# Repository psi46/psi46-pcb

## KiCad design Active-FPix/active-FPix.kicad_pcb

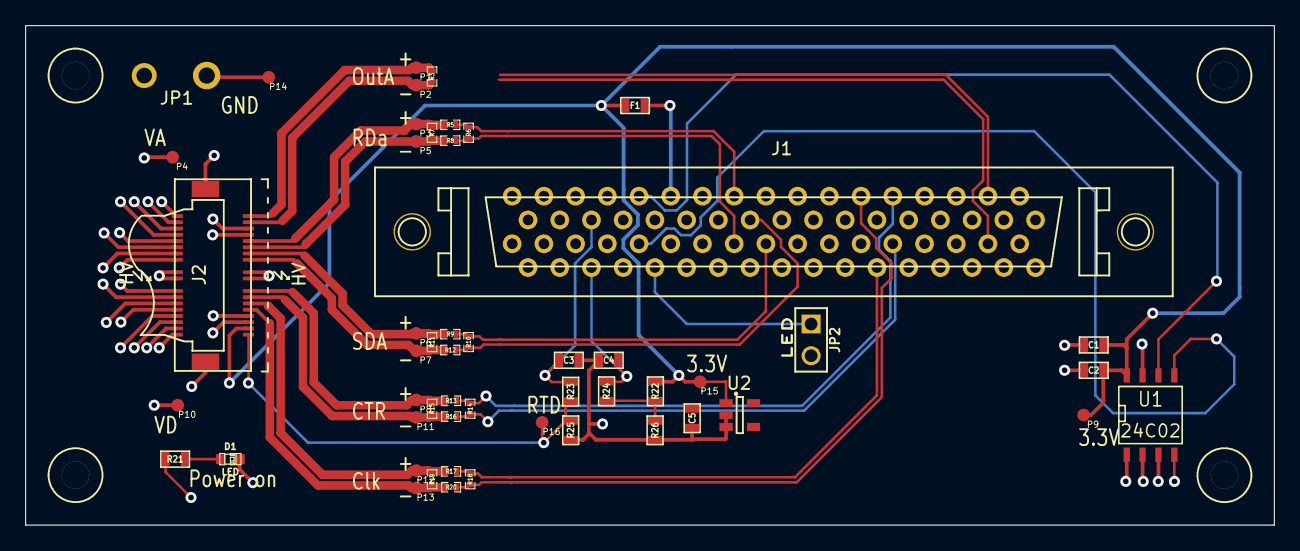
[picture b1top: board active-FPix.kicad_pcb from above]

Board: 4 copper layers, 100.0 x 40.0 mm, 56 parts (0 on the bottom side), 35 nets.

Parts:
C1, C3, C4: 100n; SM0603
C2: 1u; SM0603
C5: 1U; SM0603
D1: LED; LED-0603
F1: FUSE; SM0603
J1: CONN-SCSI68; SCSI68up
J2: CONN-SMK20; SMK20hv
JP1: JUMPER; HarwinShortLnk
JP2: JUMPER; PIN_ARRAY_2X1
P1: OutA+; testpad
P2: OutA-; testpad
P3: RDa+; testpad
P4: VA; testpad
P5: RDa-; testpad
P6: SDA+; testpad
P7: SDA-; testpad
P8: CTR+; testpad
P9: 3V3; testpad
P10: VD; testpad
P11: CTR-; testpad
P12: CLK+; testpad
P13: CLK-; testpad
P14: GND; testpad
P15: RTD+; testpad
P16: RTD-; testpad
R3: R; SM0402
R5, R8: 0; SM0402
R6, R10, R14, R18: 10G; SM0402
R7: 120; SM0402
R9, R12, R13, R16, R17, R20: 39; SM0402
R11, R15, R19: 91; SM0402
R21: 56; SM0603
R22, R25, R26: 10k 0.1%; SM0603
R23, R24: 10k 5%; SM0603
U1: 24C02; SO8N
U2: TPS769XX; SOT-23-5
loch: M2; lochM2
loch#2, loch#3, loch#4: M2; lochM2

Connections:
AIN0: C3.1, J1.57, R23.2
AIN1: C4.1, C5.1, J1.58, R24.2
CLK_n: J1.23, R18.2, R20.1
CLK_p: J1.22, R17.1, R18.1
CTR_n: J1.20, R14.2, R16.1
CTR_p: J1.19, R13.1, R14.1
GND: C1.2, C2.2, C3.2, C4.2, C5.2, J1.4, J1.6, J1.9, J1.15, J1.18, J1.21, J1.24, J1.30, J1.35, J1.38, J1.41, J1.46, J1.60, J1.64, J2.2, J2.4, J2.6, J2.8, J2.14, J2.16, J2.26, J2.28, J2.34, J2.36, J2.38, J2.40, J2.41, J2.42, JP1.1, JP1.2, P14.1, R25.2, R26.2, U1.1, U1.2, U1.3, U1.4, U1.7, U2.2, U2.3
HV: J1.68, J2.19, J2.20, J2.21, J2.22
I2C_SCL2: J1.51, U1.6
I2C_SDA2: J1.52, U1.5
unnamed: D1.1, R21.2
unnamed: F1.2, J1.47
unnamed: JP2.2, R21.1
unnamed: R22.1, R24.1, R26.1
POWER_ON: J1.50, JP2.1
RTD+: C1.1, C2.1, F1.1, J2.3, P9.1, P15.1, R22.2, U1.8, U2.1
RTD-: J2.1, P16.1, R23.1, R25.1
SDATA1_n: J1.8, R3.2
SDATA1_p: J1.7, R3.1
SDA_n: J1.37, R10.2, R12.1
SDA_p: J1.36, R9.1, R10.1
TBM_Clk_In+: J2.11, P12.1, R17.2, R19.2
TBM_Clk_In-: J2.9, P13.1, R19.1, R20.2
TBM_Out_A+: J2.39, P1.1
TBM_Out_A-: J2.37, P2.1
TBM_RDa_Out+: J2.31, P3.1, R5.2, R7.1
TBM_RDa_Out-: J2.29, P5.1, R7.2, R8.2
TBM_SD_In+: J2.27, P6.1, R9.2, R11.1
TBM_SD_In-: J2.25, P7.1, R11.2, R12.2
TBM_Trig_In+: J2.15, P8.1, R13.2, R15.1
TBM_Trig_In-: J2.13, P11.1, R15.2, R16.2
TOUT_n: J1.40, R6.2, R8.1
TOUT_p: J1.39, R5.1, R6.1
VA: J1.25, J1.26, J1.27, J1.28, J2.30, J2.32, J2.33, J2.35, P4.1
VD: J1.29, J1.42, J1.43, J1.44, J1.45, J2.5, J2.7, J2.10, J2.12, P10.1

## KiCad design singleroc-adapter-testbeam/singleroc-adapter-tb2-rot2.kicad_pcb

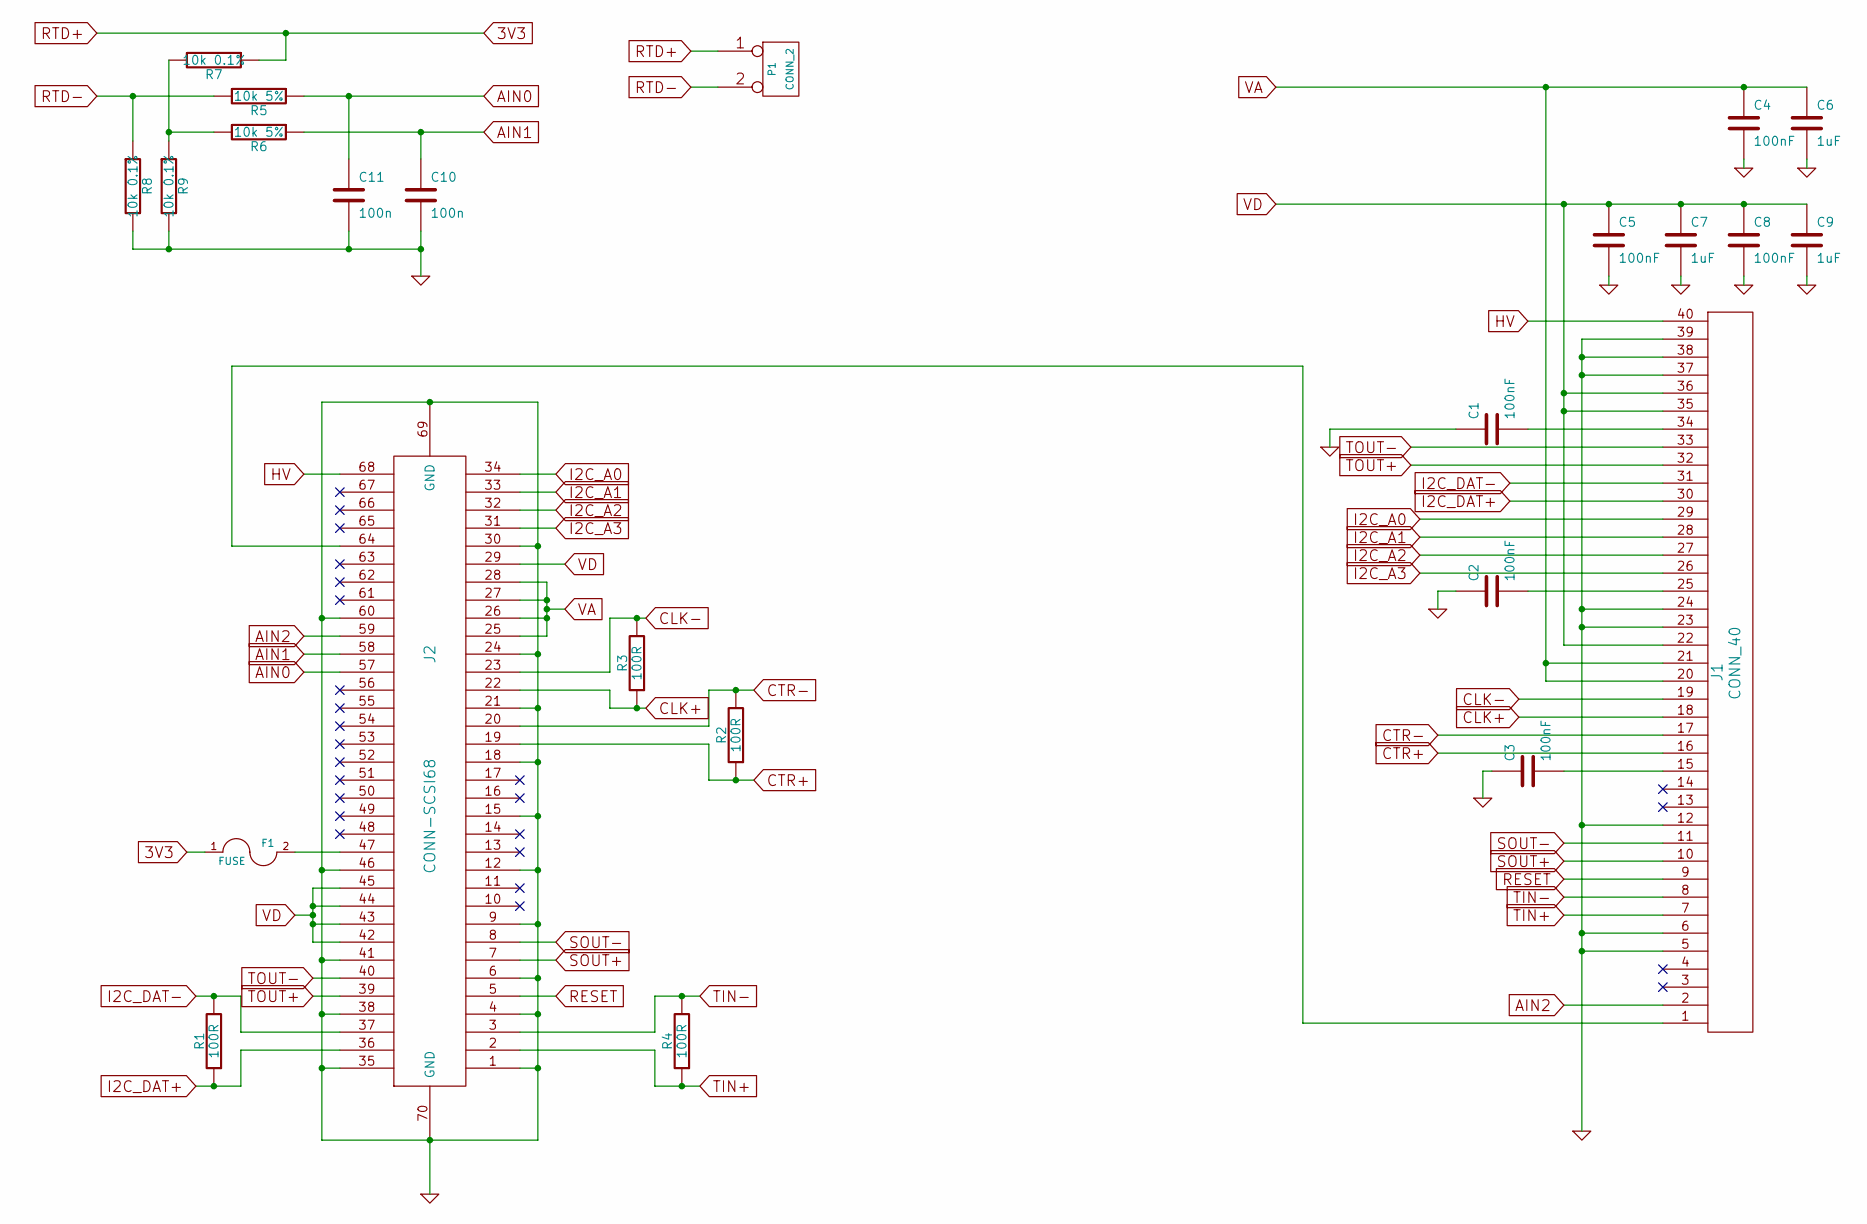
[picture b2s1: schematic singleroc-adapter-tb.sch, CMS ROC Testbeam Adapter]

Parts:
C1, C2, C3, C4, C5, C8: 100nF
C6, C7, C9: 1uF
C10, C11: 100n
F1: FUSE
J1: CONN_40
J2: CONN-SCSI68
P1: CONN_2
R1, R2, R3, R4: 100R
R5, R6: 10k 5%
R7, R8, R9: 10k 0.1%

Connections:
AIN0: C11.1, J2.57, R5.1
AIN1: C10.1, J2.58, R6.1
AIN2: J1.2, J2.59
CLK+: J1.18, J2.22, R3.1
CLK-: J1.19, J2.23, R3.2
CTR+: J1.16, J2.19, R2.1
CTR-: J1.17, J2.20, R2.2
GND: C1.1, C2.1, C3.1, C4.2, C5.2, C6.2, C7.2, C8.2, C9.2, C10.2, C11.2, J1.5, J1.6, J1.12, J1.23, J1.24, J1.37, J1.38, J1.39, J2.1, J2.4, J2.6, J2.9, J2.12, J2.15, J2.18, J2.21, J2.24, J2.30, J2.35, J2.38, J2.41, J2.46, J2.60, J2.69 (GND), J2.70 (GND), R8.2, R9.2
HV: J1.40, J2.68
I2C_A0: J1.29, J2.34
I2C_A1: J1.28, J2.33
I2C_A2: J1.27, J2.32
I2C_A3: J1.26, J2.31
I2C_DAT+: J1.30, J2.36, R1.1
I2C_DAT-: J1.31, J2.37, R1.2
unnamed: C1.2, J1.34
unnamed: C2.2, J1.25
unnamed: C3.2, J1.15
unnamed: F1.2, J2.47
unnamed: J1.1, J2.64
unnamed: R6.2, R7.2, R9.1
RESET: J1.9, J2.5
RTD+: F1.1, P1.1, R7.1
RTD-: P1.2 (PM), R5.2, R8.1
SOUT+: J1.10, J2.7
SOUT-: J1.11, J2.8
TIN+: J1.7, J2.2, R4.1
TIN-: J1.8, J2.3, R4.2
TOUT+: J1.32, J2.39
TOUT-: J1.33, J2.40
VA: C4.1, C6.1, J1.20, J1.21, J2.25, J2.26, J2.27, J2.28
VD: C5.1, C7.1, C8.1, C9.1, J1.22, J1.35, J1.36, J2.29, J2.42, J2.43, J2.44, J2.45

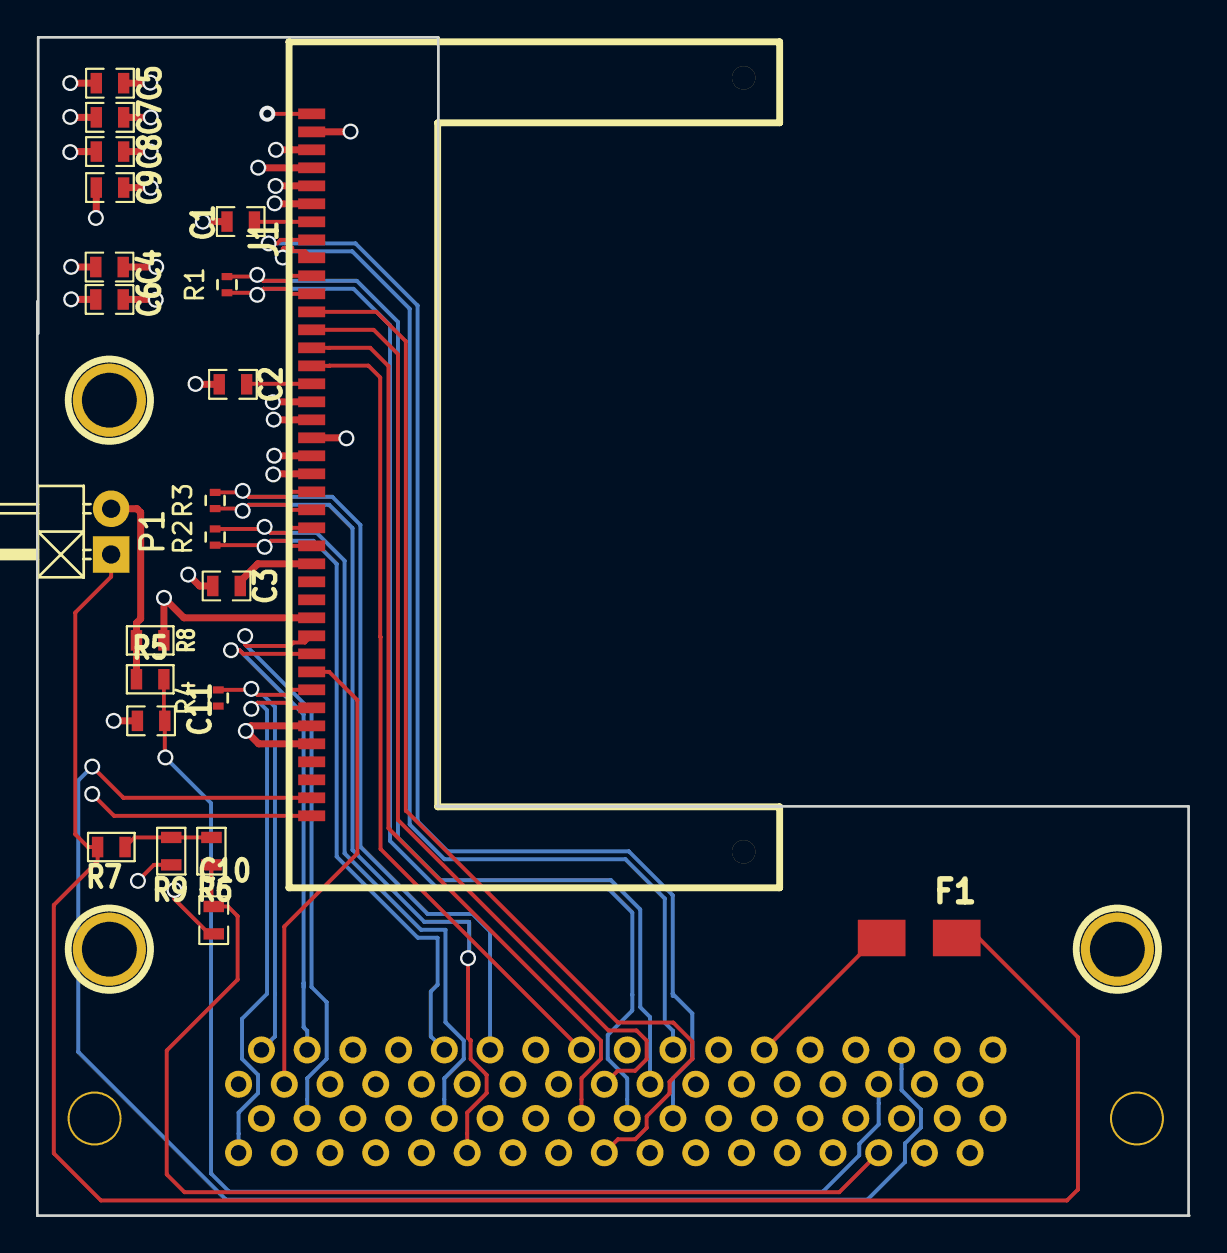
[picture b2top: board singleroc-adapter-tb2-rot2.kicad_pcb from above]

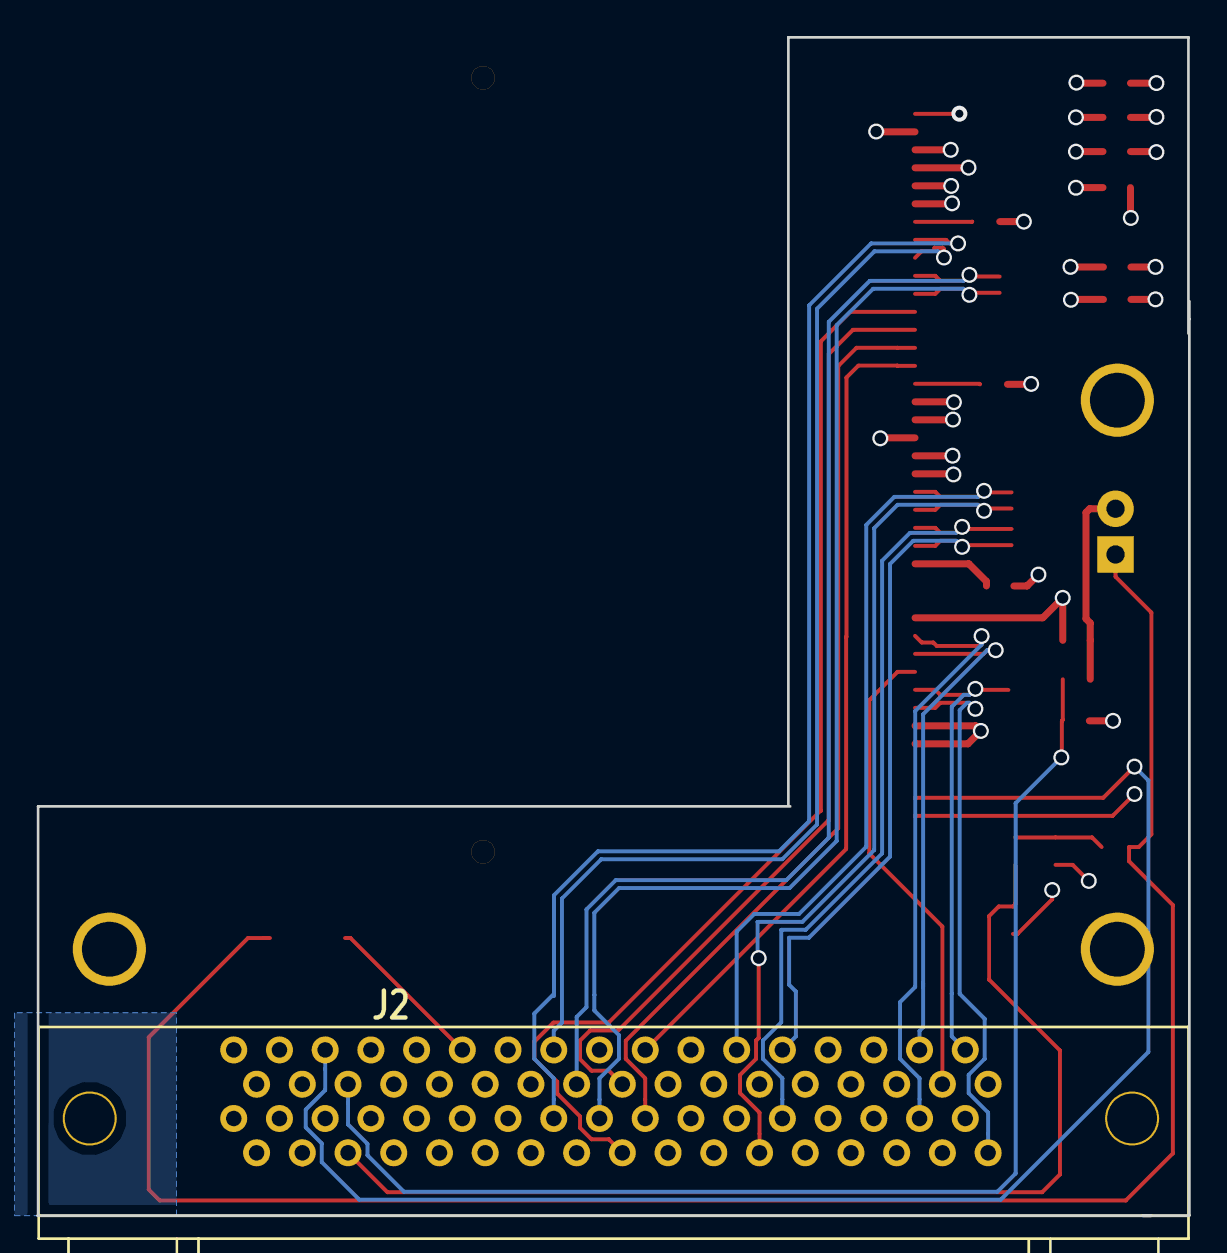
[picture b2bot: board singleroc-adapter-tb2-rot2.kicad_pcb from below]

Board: 4 copper layers, 64.0 x 65.5 mm, 24 parts (2 on the bottom side), 32 nets.

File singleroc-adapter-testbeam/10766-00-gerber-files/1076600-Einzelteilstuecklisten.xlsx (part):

DESY- ZE - AV |  |  |  |  | Baugruppenbenennung : | CMS ROC Testbeam Adapter |  |  |  |  | In Spalte (B) Bauteil Position = ist freigegeben
(C) DESY 2010, DESY behält sich alle Rechte vor. Schutzvermerk ISO 16016 beacht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 |  |  |  |  | Baugruppenenummer : |  |  |  |  |  | Gesamte Zeile = Bauteil wird nicht bestückt
 |  |  |  |  | gehört zu : |  |  |  |  |  | Kritisch |  | Geändert |  |  | Unklar
 |  |  |  |  | Ersteller : | S. Spannagel |  |  |  |  |  |  |  |  |  | RoHS Nein (X)
 |  |  |  |  | Erstellungsdatum : | 13/10/2014 |  |  |  |  |  |  |  |  |  | Bei VE = m,mm,kg oder g Menge angeben
Pos | Bauteil Position | Bauteil Art / Ort | Bau- form | Orderbase Artikelnr | Benennung / Type / Wert | Hersteller | Hersteller-Nr. | Lieferant | Lieferanten-Nr. | Preis / VE in € | Preis / n Stück | VE | Menge / VE | (X) |  | Bemerkungen
1 | J1 | T | SMD |  | Edge Connector w/ Card Guides, 40-Pin, Type 02 for 1,6mm PCBs | Samtec | MB1-140-01-L-S-02-SL | Farnell | 2097301 | 11.97 | 1 | St | 1 |  | 0
2 | J2 | B | THT |  | SCSI 68pin Connector, 90deg | Multicomp | 8AL068S-325F1-AN | Farnell | 1099270 |  | 1 | St | 1 |  | 0
3 | F1 | B | SMD |  | Fuse |  |  |  |  |  | 1 | St | 1 |  | 0 | Bauteil wird nicht bestueckt.
4 | R1 | B | SMD |  | Widerstand SMD0603 100R, Toleranz 1% | Yaego/ Vishay | RC0603FR07 100r L | ZE |  |  | 1 | St | 1 |  | 0
5 | R2 | B | SMD |  | Widerstand SMD0603 100R, Toleranz 1% | Yaego/ Vishay | RC0603FR07 100r L | ZE |  |  | 1 | St | 1 |  | 0
6 | R3 | B | SMD |  | Widerstand SMD0603 100R, Toleranz 1% | Yaego/ Vishay | RC0603FR07 100r L | ZE |  |  | 1 | St | 1 |  | 0
7 | R4 | B | SMD |  | Widerstand SMD0603 100R, Toleranz 1% | Yaego/ Vishay | RC0603FR07 100r L | ZE |  |  | 1 | St | 1 |  | 0
8 | R5 | B | SMD |  | Widerstand SMD0603 10k, Toleranz 1% | Yaego/ Vishay | RC0603FR07 10k L | ZE |  |  | 1 | St | 1 |  | 0
9 | R6 | B | SMD |  | Widerstand SMD0603 10k, Toleranz 1% | Yaego/ Vishay | RC0603FR07 10k L | ZE |  |  | 1 | St | 1 |  | 0
10 | R7 | B | SMD |  | Widerstand SMD0603 10k, Toleranz 0,1% |  |  |  |  |  | 1 | St | 1 |  | 0
11 | R8 | B | SMD |  | Widerstand SMD0603 10k, Toleranz 0,1% |  |  |  |  |  | 1 | St | 1 |  | 0
12 | R9 | B | SMD |  | Widerstand SMD0603 10k, Toleranz 0,1% |  |  |  |  |  | 1 | St | 1 |  | 0
13 | C1 | B | SMD |  | Kapazitaet SMD0603 100nF, Toleranz 10% | TDK | C1608 X7R 1H104KT | ZE |  |  | 1 | St | 1 |  | 0
14 | C2 | B | SMD |  | Kapazitaet SMD0603 100nF, Toleranz 10% | TDK | C1608 X7R 1H104KT | ZE |  |  | 1 | St | 1 |  | 0
15 | C3 | B | SMD |  | Kapazitaet SMD0603 100nF, Toleranz 10% | TDK | C1608 X7R 1H104KT | ZE |  |  | 1 | St | 1 |  | 0
16 | C4 | B | SMD |  | Kapazitaet SMD0603 100nF, Toleranz 10% | TDK | C1608 X7R 1H104KT | ZE |  |  | 1 | St | 1 |  | 0
17 | C5 | B | SMD |  | Kapazitaet SMD0603 100nF, Toleranz 10% | TDK | C1608 X7R 1H104KT | ZE |  |  | 1 | St | 1 |  | 0
18 | C6 | B | SMD |  | Kapazitaet SMD0603 1uF, Toleranz 10% |  |  |  |  |  | 1 | St | 1 |  | 0
19 | C7 | B | SMD |  | Kapazitaet SMD0603 1uF, Toleranz 10% |  |  |  |  |  | 1 | St | 1 |  | 0
20 | C8 | B | SMD |  | Kapazitaet SMD0603 100nF, Toleranz 10% | TDK | C1608 X7R 1H104KT | ZE |  |  | 1 | St | 1 |  | 0
21 | C9 | B | SMD |  | Kapazitaet SMD0603 1uF, Toleranz 10% |  |  |  |  |  | 1 | St | 1 |  | 0
22 | C10 | B | SMD |  | Kapazitaet SMD0603 100nF, Toleranz 10% | TDK | C1608 X7R 1H104KT | ZE |  |  | 1 | St | 1 |  | 0
23 | C11 | B | SMD |  | Kapazitaet SMD0603 100nF, Toleranz 10% | TDK | C1608 X7R 1H104KT | ZE |  |  | 1 | St | 1 |  | 0
24 | P1 | B | THT |  | Stiftleiste, 1x2 Pins, 90deg, Pitch 2,54mm | Molex | 22-12-4022 | Farnell | 1360142 |  | 1 | St | 1 |  | 0
25 |  | LP |  |  | Leiterplatte 10766-00 |  |  |  |  |  | 1 | St | 1 |  | 0
26 |  |  |  |  |  |  |  |  |  |  | 1 | St | 1 |  | 0
27 |  |  |  |  |  |  |  |  |  |  | 1 | St | 1 |  | 0
28 |  |  |  |  |  |  |  |  |  |  | 1 | St | 1 |  | 0
29 |  |  |  |  |  |  |  |  |  |  | 1 | St | 1 |  | 0
30 |  |  |  |  |  |  |  |  |  |  | 1 | St | 1 |  | 0
31 |  |  |  |  |  |  |  |  |  |  | 1 | St | 1 |  | 0
32 |  |  |  |  |  |  |  |  |  |  | 1 | St | 1 |  | 0
33 |  |  |  |  |  |  |  |  |  |  | 1 | St | 1 |  | 0
34 |  |  |  |  |  |  |  |  |  |  | 1 | St | 1 |  | 0
35 |  |  |  |  |  |  |  |  |  |  | 1 | St | 1 |  | 0
36 |  |  |  |  |  |  |  |  |  |  | 1 | St | 1 |  | 0
37 |  |  |  |  |  |  |  |  |  |  | 1 | St | 1 |  | 0
38 |  |  |  |  |  |  |  |  |  |  | 1 | St | 1 |  | 0
39 |  |  |  |  |  |  |  |  |  |  | 1 | St | 1 |  | 0
40 |  |  |  |  |  |  |  |  |  |  | 1 | St | 1 |  | 0
41 |  |  |  |  |  |  |  |  |  |  | 1 | St | 1 |  | 0
42 |  |  |  |  |  |  |  |  |  |  | 1 | St | 1 |  | 0
43 |  |  |  |  |  |  |  |  |  |  | 1 | St | 1 |  | 0
44 |  |  |  |  |  |  |  |  |  |  | 1 | St | 1 |  | 0
45 |  |  |  |  |  |  |  |  |  |  | 1 | St | 1 |  | 0
46 |  |  |  |  |  |  |  |  |  |  | 1 | St | 1 |  | 0
47 |  |  |  |  |  |  |  |  |  |  | 1 | St | 1 |  | 0
48 |  |  |  |  |  |  |  |  |  |  | 1 | St | 1 |  | 0
49 |  |  |  |  |  |  |  |  |  |  | 1 | St | 1 |  | 0
50 |  |  |  |  |  |  |  |  |  |  | 1 | St | 1 |  | 0
51 |  |  |  |  |  |  |  |  |  |  | 1 | St | 1 |  | 0
52 |  |  |  |  |  |  |  |  |  |  | 1 | St | 1 |  | 0
53 |  |  |  |  |  |  |  |  |  |  | 1 | St | 1 |  | 0
54 |  |  |  |  |  |  |  |  |  |  | 1 | St | 1 |  | 0
55 |  |  |  |  |  |  |  |  |  |  | 1 | St | 1 |  | 0
56 |  |  |  |  |  |  |  |  |  |  | 1 | St | 1 |  | 0
57 |  |  |  |  |  |  |  |  |  |  | 1 | St | 1 |  | 0
58 |  |  |  |  |  |  |  |  |  |  | 1 | St | 1 |  | 0
59 |  |  |  |  |  |  |  |  |  |  | 1 | St | 1 |  | 0
60 |  |  |  |  |  |  |  |  |  |  | 1 | St | 1 |  | 0
61 |  |  |  |  |  |  |  |  |  |  | 1 | St | 1 |  | 0
62 |  |  |  |  |  |  |  |  |  |  | 1 | St | 1 |  | 0
63 |  |  |  |  |  |  |  |  |  |  | 1 | St | 1 |  | 0
64 |  |  |  |  |  |  |  |  |  |  | 1 | St | 1 |  | 0
65 |  |  |  |  |  |  |  |  |  |  | 1 | St | 1 |  | 0
66 |  |  |  |  |  |  |  |  |  |  | 1 | St | 1 |  | 0
67 |  |  |  |  |  |  |  |  |  |  | 1 | St | 1 |  | 0
68 |  |  |  |  |  |  |  |  |  |  | 1 | St | 1 |  | 0
69 |  |  |  |  |  |  |  |  |  |  | 1 | St | 1 |  | 0
70 |  |  |  |  |  |  |  |  |  |  | 1 | St | 1 |  | 0
71 |  |  |  |  |  |  |  |  |  |  | 1 | St | 1 |  | 0
72 |  |  |  |  |  |  |  |  |  |  | 1 | St | 1 |  | 0
73 |  |  |  |  |  |  |  |  |  |  | 1 | St | 1 |  | 0
74 |  |  |  |  |  |  |  |  |  |  | 1 | St | 1 |  | 0
75 |  |  |  |  |  |  |  |  |  |  | 1 | St | 1 |  | 0
76 |  |  |  |  |  |  |  |  |  |  | 1 | St | 1 |  | 0
77 |  |  |  |  |  |  |  |  |  |  | 1 | St | 1 |  | 0
78 |  |  |  |  |  |  |  |  |  |  | 1 | St | 1 |  | 0
79 |  |  |  |  |  |  |  |  |  |  | 1 | St | 1 |  | 0
80 |  |  |  |  |  |  |  |  |  |  | 1 | St | 1 |  | 0
81 |  |  |  |  |  |  |  |  |  |  | 1 | St | 1 |  | 0
82 |  |  |  |  |  |  |  |  |  |  | 1 | St | 1 |  | 0
83 |  |  |  |  |  |  |  |  |  |  | 1 | St | 1 |  | 0
84 |  |  |  |  |  |  |  |  |  |  | 1 | St | 1 |  | 0
85 |  |  |  |  |  |  |  |  |  |  | 1 | St | 1 |  | 0
86 |  |  |  |  |  |  |  |  |  |  | 1 | St | 1 |  | 0
87 |  |  |  |  |  |  |  |  |  |  | 1 | St | 1 |  | 0
88 |  |  |  |  |  |  |  |  |  |  | 1 | St | 1 |  | 0
89 |  |  |  |  |  |  |  |  |  |  | 1 | St | 1 |  | 0
90 |  |  |  |  |  |  |  |  |  |  | 1 | St | 1 |  | 0
91 |  |  |  |  |  |  |  |  |  |  | 1 | St | 1 |  | 0
92 |  |  |  |  |  |  |  |  |  |  | 1 | St | 1 |  | 0
93 |  |  |  |  |  |  |  |  |  |  | 1 | St | 1 |  | 0
94 |  |  |  |  |  |  |  |  |  |  | 1 | St | 1 |  | 0
95 |  |  |  |  |  |  |  |  |  |  | 1 | St | 1 |  | 0
96 |  |  |  |  |  |  |  |  |  |  | 1 | St | 1 |  | 0
97 |  |  |  |  |  |  |  |  |  |  | 1 | St | 1 |  | 0
98 |  |  |  |  |  |  |  |  |  |  | 1 | St | 1 |  | 0
99 |  |  |  |  |  |  |  |  |  |  | 1 | St | 1 |  | 0
100 |  |  |  |  |  |  |  |  |  |  | 1 | St | 1 |  | 0
101 |  |  |  |  |  |  |  |  |  |  | 1 | St | 1 |  | 0
102 |  |  |  |  |  |  |  |  |  |  | 1 | St | 1 |  | 0
103 |  |  |  |  |  |  |  |  |  |  | 1 | St | 1 |  | 0
104 |  |  |  |  |  |  |  |  |  |  | 1 | St | 1 |  | 0
105 |  |  |  |  |  |  |  |  |  |  | 1 | St | 1 |  | 0
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
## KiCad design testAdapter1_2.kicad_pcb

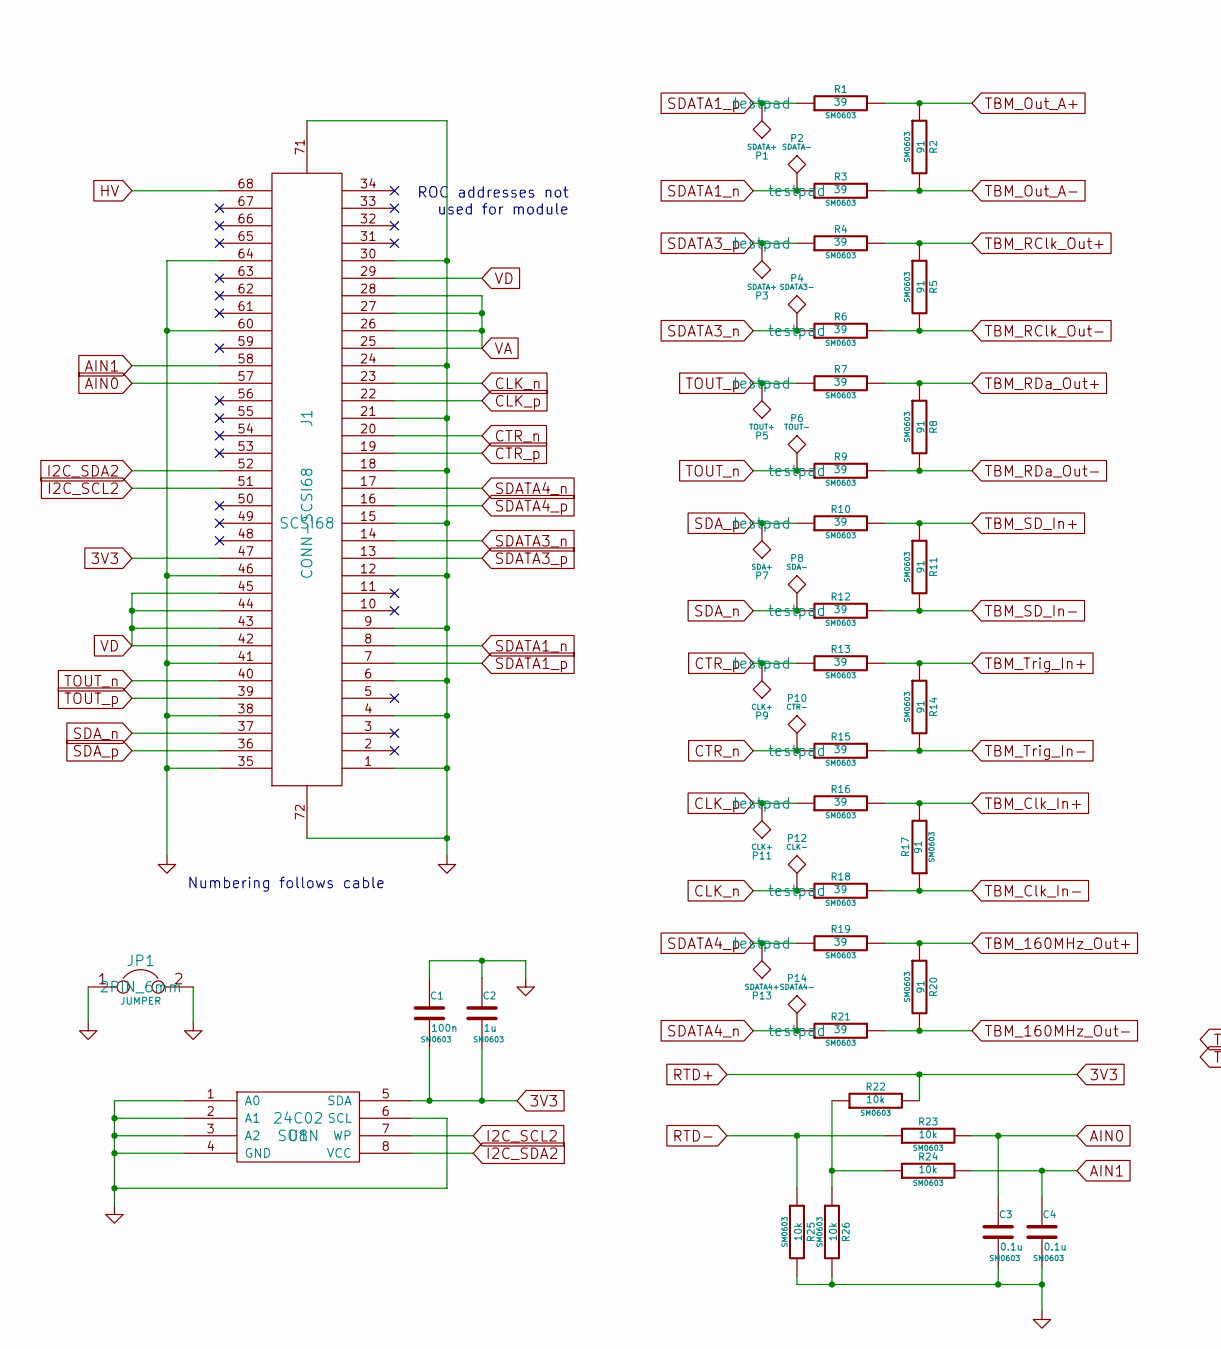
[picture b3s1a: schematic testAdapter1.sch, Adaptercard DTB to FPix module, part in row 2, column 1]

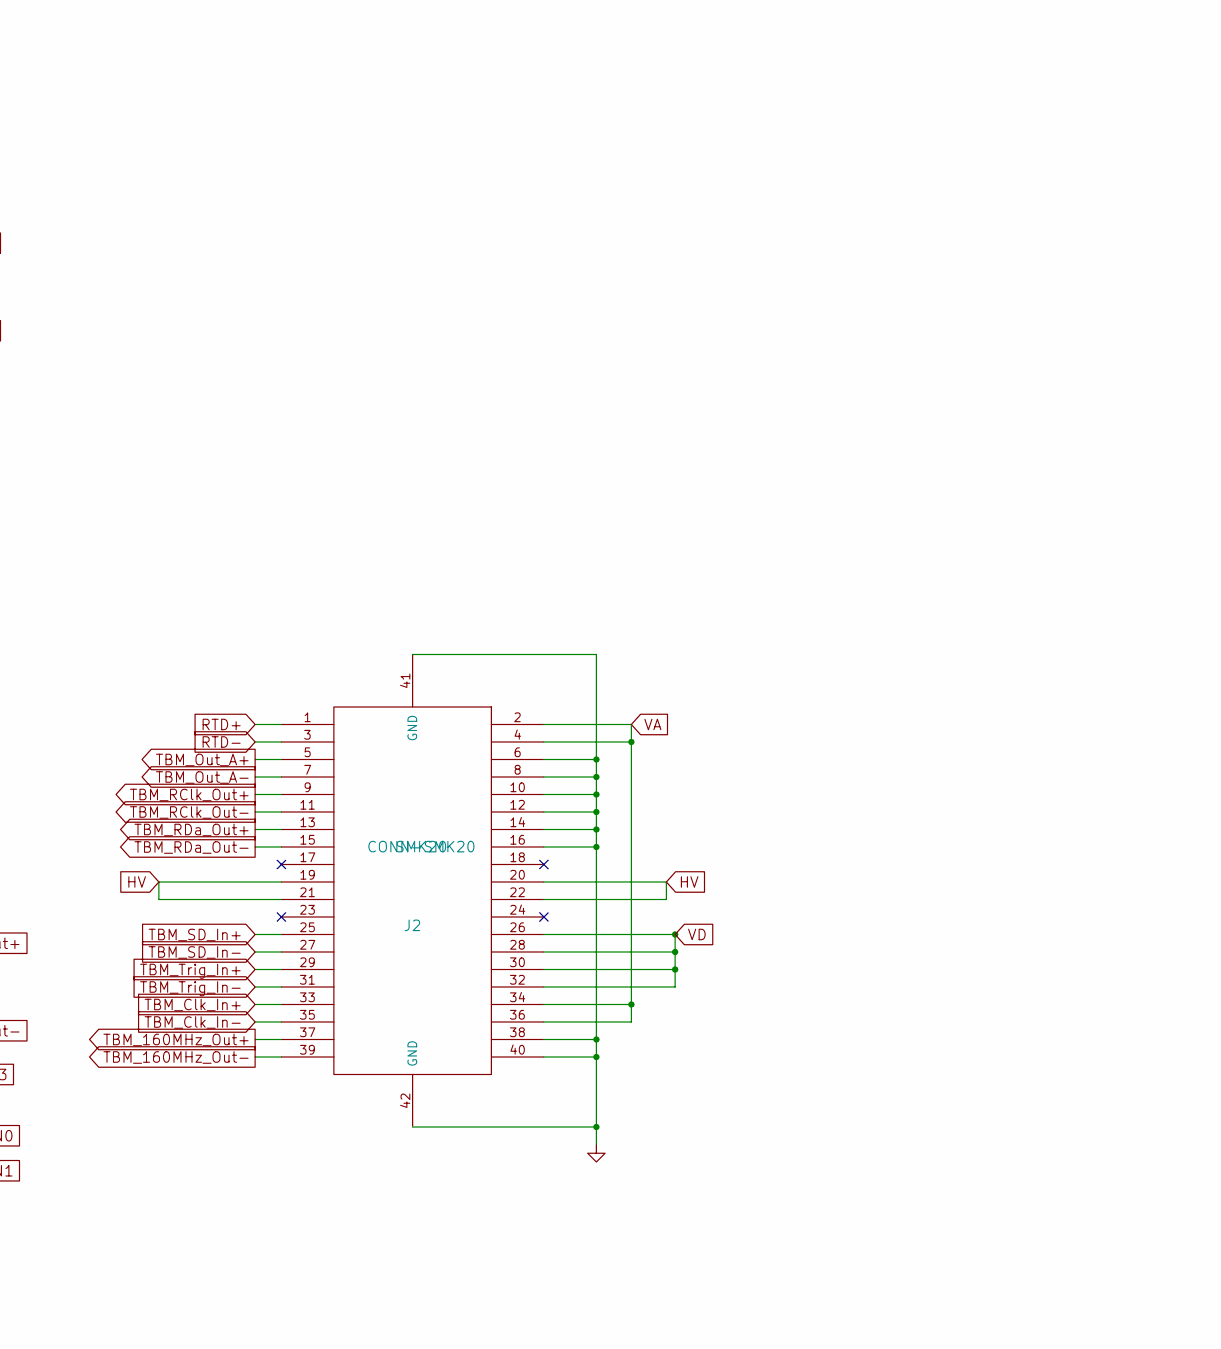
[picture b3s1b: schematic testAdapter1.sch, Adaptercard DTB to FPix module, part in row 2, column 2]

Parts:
C1: 100n; SM0603
C2: 1u; SM0603
C3, C4: 0.1u; SM0603
J1: CONN-SCSI68; SCSI68
J2: CONN-SMK20; SMK20
JP1: JUMPER; 2PIN_6mm
P1, P3: SDATA+; testpad
P2: SDATA-; testpad
P4: SDATA3-; testpad
P5: TOUT+; testpad
P6: TOUT-; testpad
P7: SDA+; testpad
P8: SDA-; testpad
P9, P11: CLK+; testpad
P10: CTR-; testpad
P12: CLK-; testpad
P13: SDATA4+; testpad
P14: SDATA4-; testpad
R1, R3, R4, R6, R7, R9, R10, R12, R13, R15, R16, R18, R19, R21: 39; SM0603
R2, R5, R8, R11, R14, R17, R20: 91; SM0603
R22, R23, R24, R25, R26: 10k; SM0603
U1: 24C02; SO8N

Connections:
3V3: C1.2, C2.2, J1.47, J2.1, R22.2, U1.5 (SDA)
AIN0: C3.1, J1.57, R23.2
AIN1: C4.1, J1.58, R24.2
CLK_n: J1.23, P12.1, R18.1
CLK_p: J1.22, P11.1, R16.1
CTR_n: J1.20, P10.1, R15.1
CTR_p: J1.19, P9.1, R13.1
GND: C1.1, C2.1, C3.2, C4.2, J1.1, J1.4, J1.6, J1.9, J1.12, J1.15, J1.18, J1.21, J1.24, J1.30, J1.35, J1.38, J1.41, J1.46, J1.60, J1.64, J1.71, J1.72, J2.6, J2.8, J2.10, J2.12, J2.14, J2.16, J2.38, J2.40, J2.41 (GND), J2.42 (GND), JP1.1, JP1.2, R25.2, R26.2, U1.1 (A0), U1.2 (A1), U1.3 (A2), U1.4 (GND), U1.6 (SCL)
HV: J1.68, J2.19, J2.20, J2.21, J2.22
I2C_SCL2: J1.51, U1.7 (WP)
I2C_SDA2: J1.52, U1.8 (VCC)
unnamed: R22.1, R24.1, R26.1
RTD-: J2.3, R23.1, R25.1
SDATA1_n: J1.8, P2.1, R3.1
SDATA1_p: J1.7, P1.1, R1.1
SDATA3_n: J1.14, P4.1, R6.1
SDATA3_p: J1.13, P3.1, R4.1
SDATA4_n: J1.17, P14.1, R21.1
SDATA4_p: J1.16, P13.1, R19.1
SDA_n: J1.37, P8.1, R12.1
SDA_p: J1.36, P7.1, R10.1
TBM_160MHz_Out+: J2.37, R19.2, R20.1
TBM_160MHz_Out-: J2.39, R20.2, R21.2
TBM_Clk_In+: J2.33, R16.2, R17.2
TBM_Clk_In-: J2.35, R17.1, R18.2
TBM_Out_A+: J2.5, R1.2, R2.1
TBM_Out_A-: J2.7, R2.2, R3.2
TBM_RClk_Out+: J2.9, R4.2, R5.1
TBM_RClk_Out-: J2.11, R5.2, R6.2
TBM_RDa_Out+: J2.13, R7.2, R8.1
TBM_RDa_Out-: J2.15, R8.2, R9.2
TBM_SD_In+: J2.25, R10.2, R11.1
TBM_SD_In-: J2.27, R11.2, R12.2
TBM_Trig_In+: J2.29, R13.2, R14.1
TBM_Trig_In-: J2.31, R14.2, R15.2
TOUT_n: J1.40, P6.1, R9.1
TOUT_p: J1.39, P5.1, R7.1
VA: J1.25, J1.26, J1.27, J1.28, J2.2, J2.4, J2.34, J2.36
VD: J1.29, J1.42, J1.43, J1.44, J1.45, J2.26, J2.28, J2.30, J2.32

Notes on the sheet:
Numbering follows cable
ROC addresses not used for module

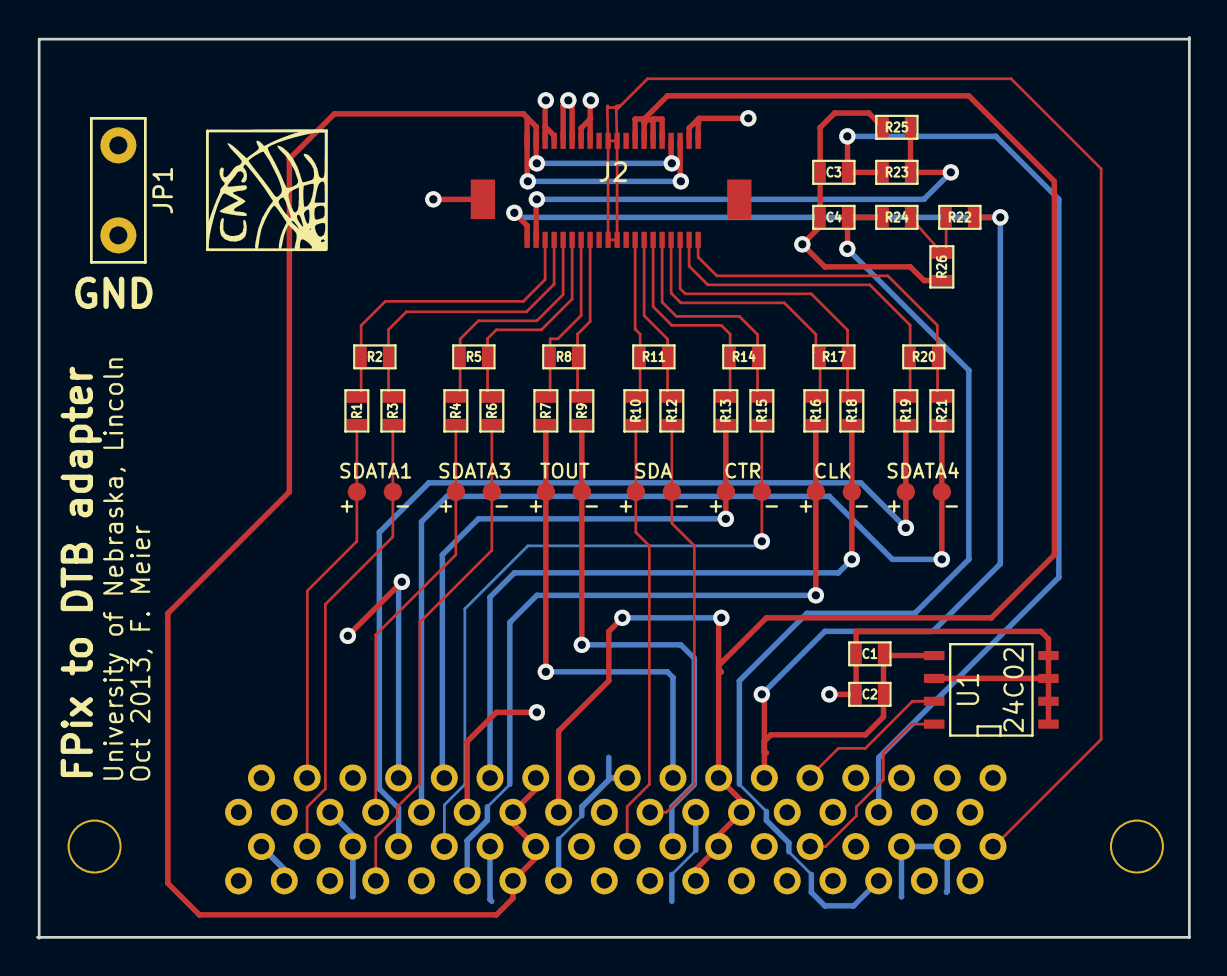
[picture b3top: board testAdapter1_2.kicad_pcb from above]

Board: 2 copper layers, 64.0 x 50.1 mm, 48 parts (1 on the bottom side), 39 nets.
